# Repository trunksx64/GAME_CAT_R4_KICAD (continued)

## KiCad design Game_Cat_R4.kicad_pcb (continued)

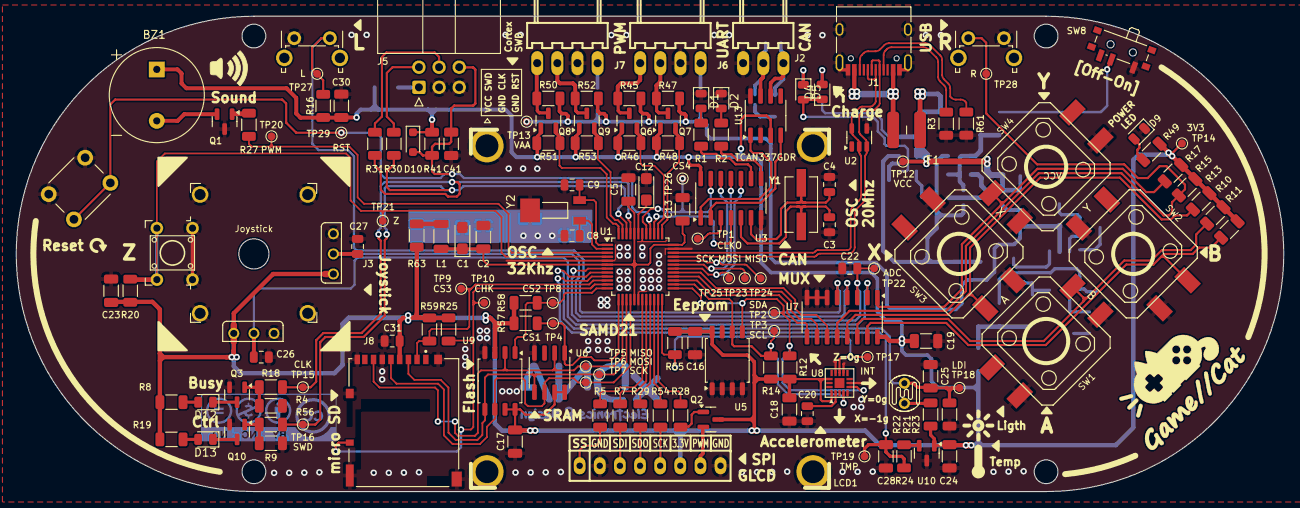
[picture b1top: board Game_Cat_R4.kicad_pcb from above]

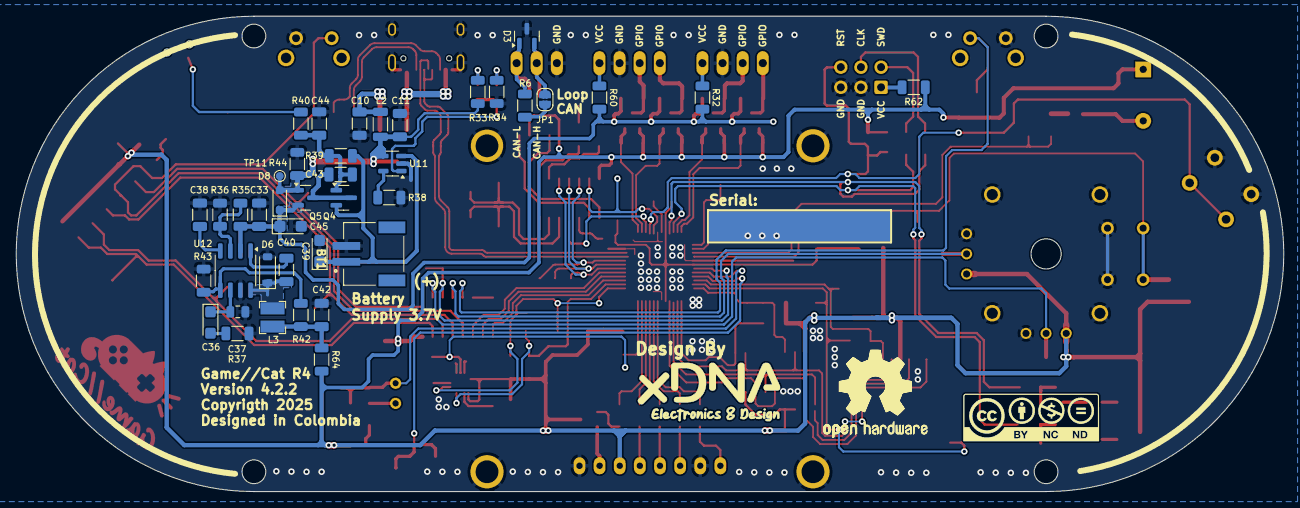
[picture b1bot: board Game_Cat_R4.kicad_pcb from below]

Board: 2 copper layers, 160.0 x 60.0 mm, 186 parts (40 on the bottom side), 113 nets.

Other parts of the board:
C43, C44: 100nF; C_1206_3216Metric

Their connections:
/POWER SUPPLY/BRG: C43.1; also elsewhere on the board
/POWER SUPPLY/M: C43.2, C44.1; also elsewhere on the board
GND: C44.2; also elsewhere on the board

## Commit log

2022-11-27 26/11/22/A
2022-12-15 14/12/22/A
2022-12-18 18/12/22/A
2022-12-19 19/12/22/A
2022-12-21 21/12/22/A
2023-03-25 24/03/23/A
2023-12-26 26/12/13/A
2024-06-08 08/06/24/A
2025-01-24 25/01/24/A
2025-01-24 25/01/24/B
2025-01-24 25/01/24/C
2025-01-26 25/01/26/A
2025-01-26 25/01/26/B
2025-05-26 05/25/25/A
2026-03-11 03/11/26/Update BOM & Models VRML
2026-03-11 03/12/26/Update BOM & Models VRML
